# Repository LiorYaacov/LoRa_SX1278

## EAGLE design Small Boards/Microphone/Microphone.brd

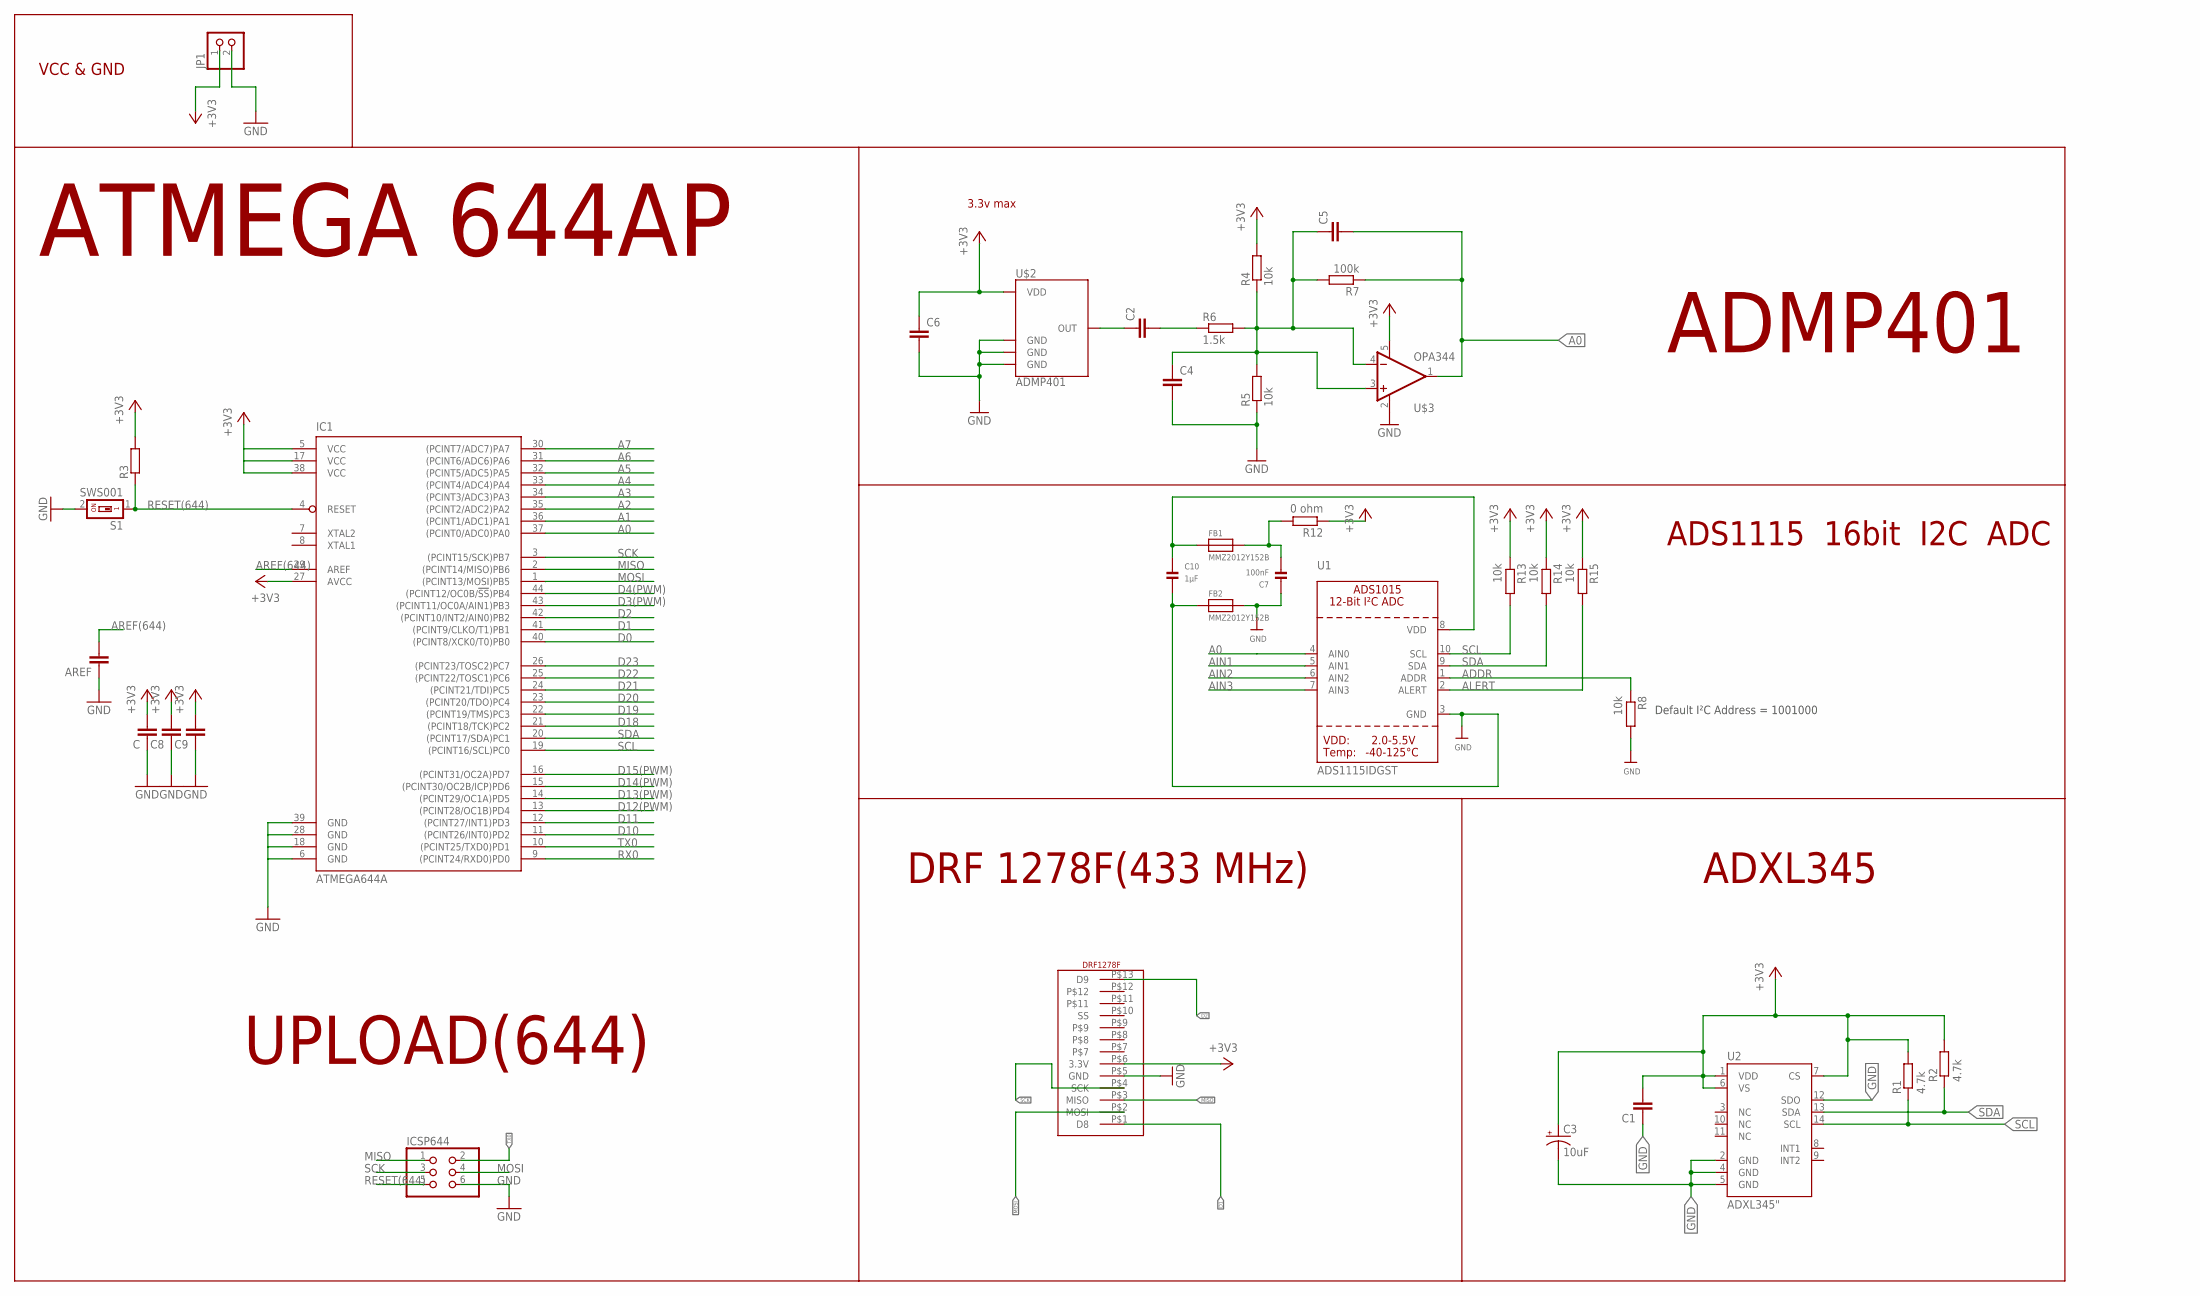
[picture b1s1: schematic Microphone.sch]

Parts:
AREF: 100nF; C0805
C: 22 uF; C0805
C1, C6: 0.1uF; C0805
C2: 4.7uF; C0805
C3: 10uF; EIA3216
C4: 1uF; C0805
C5: 100pF; C0805
C7: 100nF; 0805
C8, C9: 100nF; C0805
C10: 1µF; 0805
FB1, FB2: MMZ2012Y152B; 0805
IC1: ATMEGA644A; TQFP44
ICSP644: PINHD-2X3; 2X03
JP1: PINHD-1X2; 1X02
R1, R2: 4.7k; R0805
R3: R-EU_R0805; R0805
R4, R5, R8, R13, R14, R15: 10k; R0805
R6: 1.5k; R0805
R7: 100k; R0805
R12: 0 ohm; R0805
S1: SWS001; SMS-001
U1: ADS1115IDGST; MSOP10
U2: ADXL345"; ADXL3451:1
U$1: DRF1278F; DIP13
U$2: ADMP401
U$3: OPA344; SOT23-5

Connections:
+3V3: C.2, C1.2, C3.A (+), C6.1, C8.2, C9.2, IC1.5 (VCC), IC1.17 (VCC), IC1.27 (AVCC), IC1.38 (VCC), JP1.1, R1.2, R2.2, R3.2, R4.2, R12.1, R13.1, R14.1, R15.1, U2.1 (VDD), U2.6 (VS), U2.7 (CS), U$1.P$6 (3.3V), U$2.5 (VDD), U$3.5 (V+)
A0: C5.2, IC1.37 ((PCINT0/ADC0)PA0), R7.1, U1.4 (AIN0), U$3.1 (OUT)
A1: IC1.36 ((PCINT1/ADC1)PA1)
A2: IC1.35 ((PCINT2/ADC2)PA2)
A3: IC1.34 ((PCINT3/ADC3)PA3)
A4: IC1.33 ((PCINT4/ADC4)PA4)
A5: IC1.32 ((PCINT5/ADC5)PA5)
A6: IC1.31 ((PCINT6/ADC6)PA6)
A7: IC1.30 ((PCINT7/ADC7)PA7)
ADDR: R8.1, U1.1 (ADDR)
AIN1: U1.5 (AIN1)
AIN2: U1.6 (AIN2)
AIN3: U1.7 (AIN3)
ALERT: R15.2, U1.2 (ALERT)
AREF(644): AREF.2, IC1.29 (AREF)
D0: IC1.40 ((PCINT8/XCK0/T0)PB0)
D1: IC1.41 ((PCINT9/CLKO/T1)PB1), U$1.P$1 (D8)
D2: IC1.42 ((PCINT10/INT2/AIN0)PB2), U$1.P$13 (D9)
D3(PWM): IC1.43 ((PCINT11/OC0A/AIN1)PB3)
D4(PWM): IC1.44 ((PCINT12/OC0B/!SS!)PB4)
D10: IC1.11 ((PCINT26/INT0)PD2)
D11: IC1.12 ((PCINT27/INT1)PD3)
D12(PWM): IC1.13 ((PCINT28/OC1B)PD4)
D13(PWM): IC1.14 ((PCINT29/OC1A)PD5)
D14(PWM): IC1.15 ((PCINT30/OC2B/ICP)PD6)
D15(PWM): IC1.16 ((PCINT31/OC2A)PD7)
D18: IC1.21 ((PCINT18/TCK)PC2)
D19: IC1.22 ((PCINT19/TMS)PC3)
D20: IC1.23 ((PCINT20/TDO)PC4)
D21: IC1.24 ((PCINT21/TDI)PC5)
D22: IC1.25 ((PCINT22/TOSC1)PC6)
D23: IC1.26 ((PCINT23/TOSC2)PC7)
GND: AREF.1, C.1, C1.1, C3.C (-), C4.2, C6.2, C7.1, C8.1, C9.1, C10.2, FB2.1, FB2.2, IC1.6 (GND), IC1.18 (GND), IC1.28 (GND), IC1.39 (GND), ICSP644.6, JP1.2, R5.1, R8.2, S1.2, U1.3 (GND), U2.2 (GND), U2.4 (GND), U2.5 (GND), U2.12 (SDO), U$1.P$5 (GND), U$2.2 (GND), U$2.4 (GND), U$2.6 (GND), U$3.2 (V-)
MISO: IC1.2 ((PCINT14/MISO)PB6), ICSP644.1, U$1.P$3 (MISO)
MOSI: IC1.1 ((PCINT13/MOSI)PB5), ICSP644.4, U$1.P$2 (MOSI)
unnamed: C2.1, U$2.1 (OUT)
unnamed: C2.2, R6.1
unnamed: C4.1, C5.1, R4.1, R5.2, R6.2, R7.2, U$3.3 (+IN), U$3.4 (-IN)
unnamed: C7.2, FB1.2, R12.2
unnamed: C10.1, FB1.1, U1.8 (VDD)
RESET(644): IC1.4 (RESET), ICSP644.5, R3.1, S1.1
RX0: IC1.9 ((PCINT24/RXD0)PD0)
SCK: IC1.3 ((PCINT15/SCK)PB7), ICSP644.3, U$1.P$4 (SCK)
SCL: IC1.19 ((PCINT16/SCL)PC0), R1.1, R13.2, U1.10 (SCL), U2.14 (SCL)
SDA: IC1.20 ((PCINT17/SDA)PC1), R2.1, R14.2, U1.9 (SDA), U2.13 (SDA)
TX0: IC1.10 ((PCINT25/TXD0)PD1), ICSP644.2

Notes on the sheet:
ATMEGA 644AP
UPLOAD(644)
ADXL345
DRF 1278F(433 MHz)
VCC & GND
ADMP401
Default I²C Address = 1001000
ADS1115 16bit I2C ADC
3.3v max

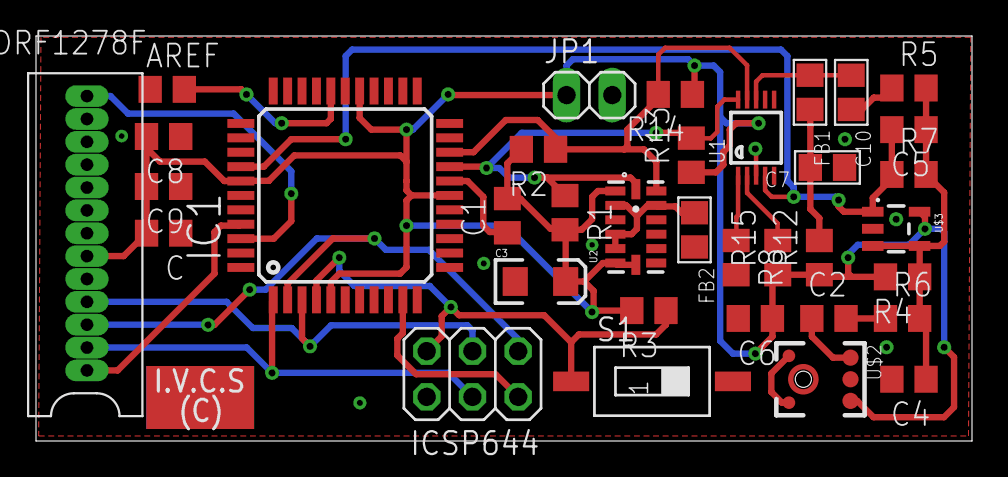
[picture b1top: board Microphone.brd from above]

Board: 2 copper layers, 52.0 x 22.5 mm, 35 parts (0 on the bottom side), 20 nets.

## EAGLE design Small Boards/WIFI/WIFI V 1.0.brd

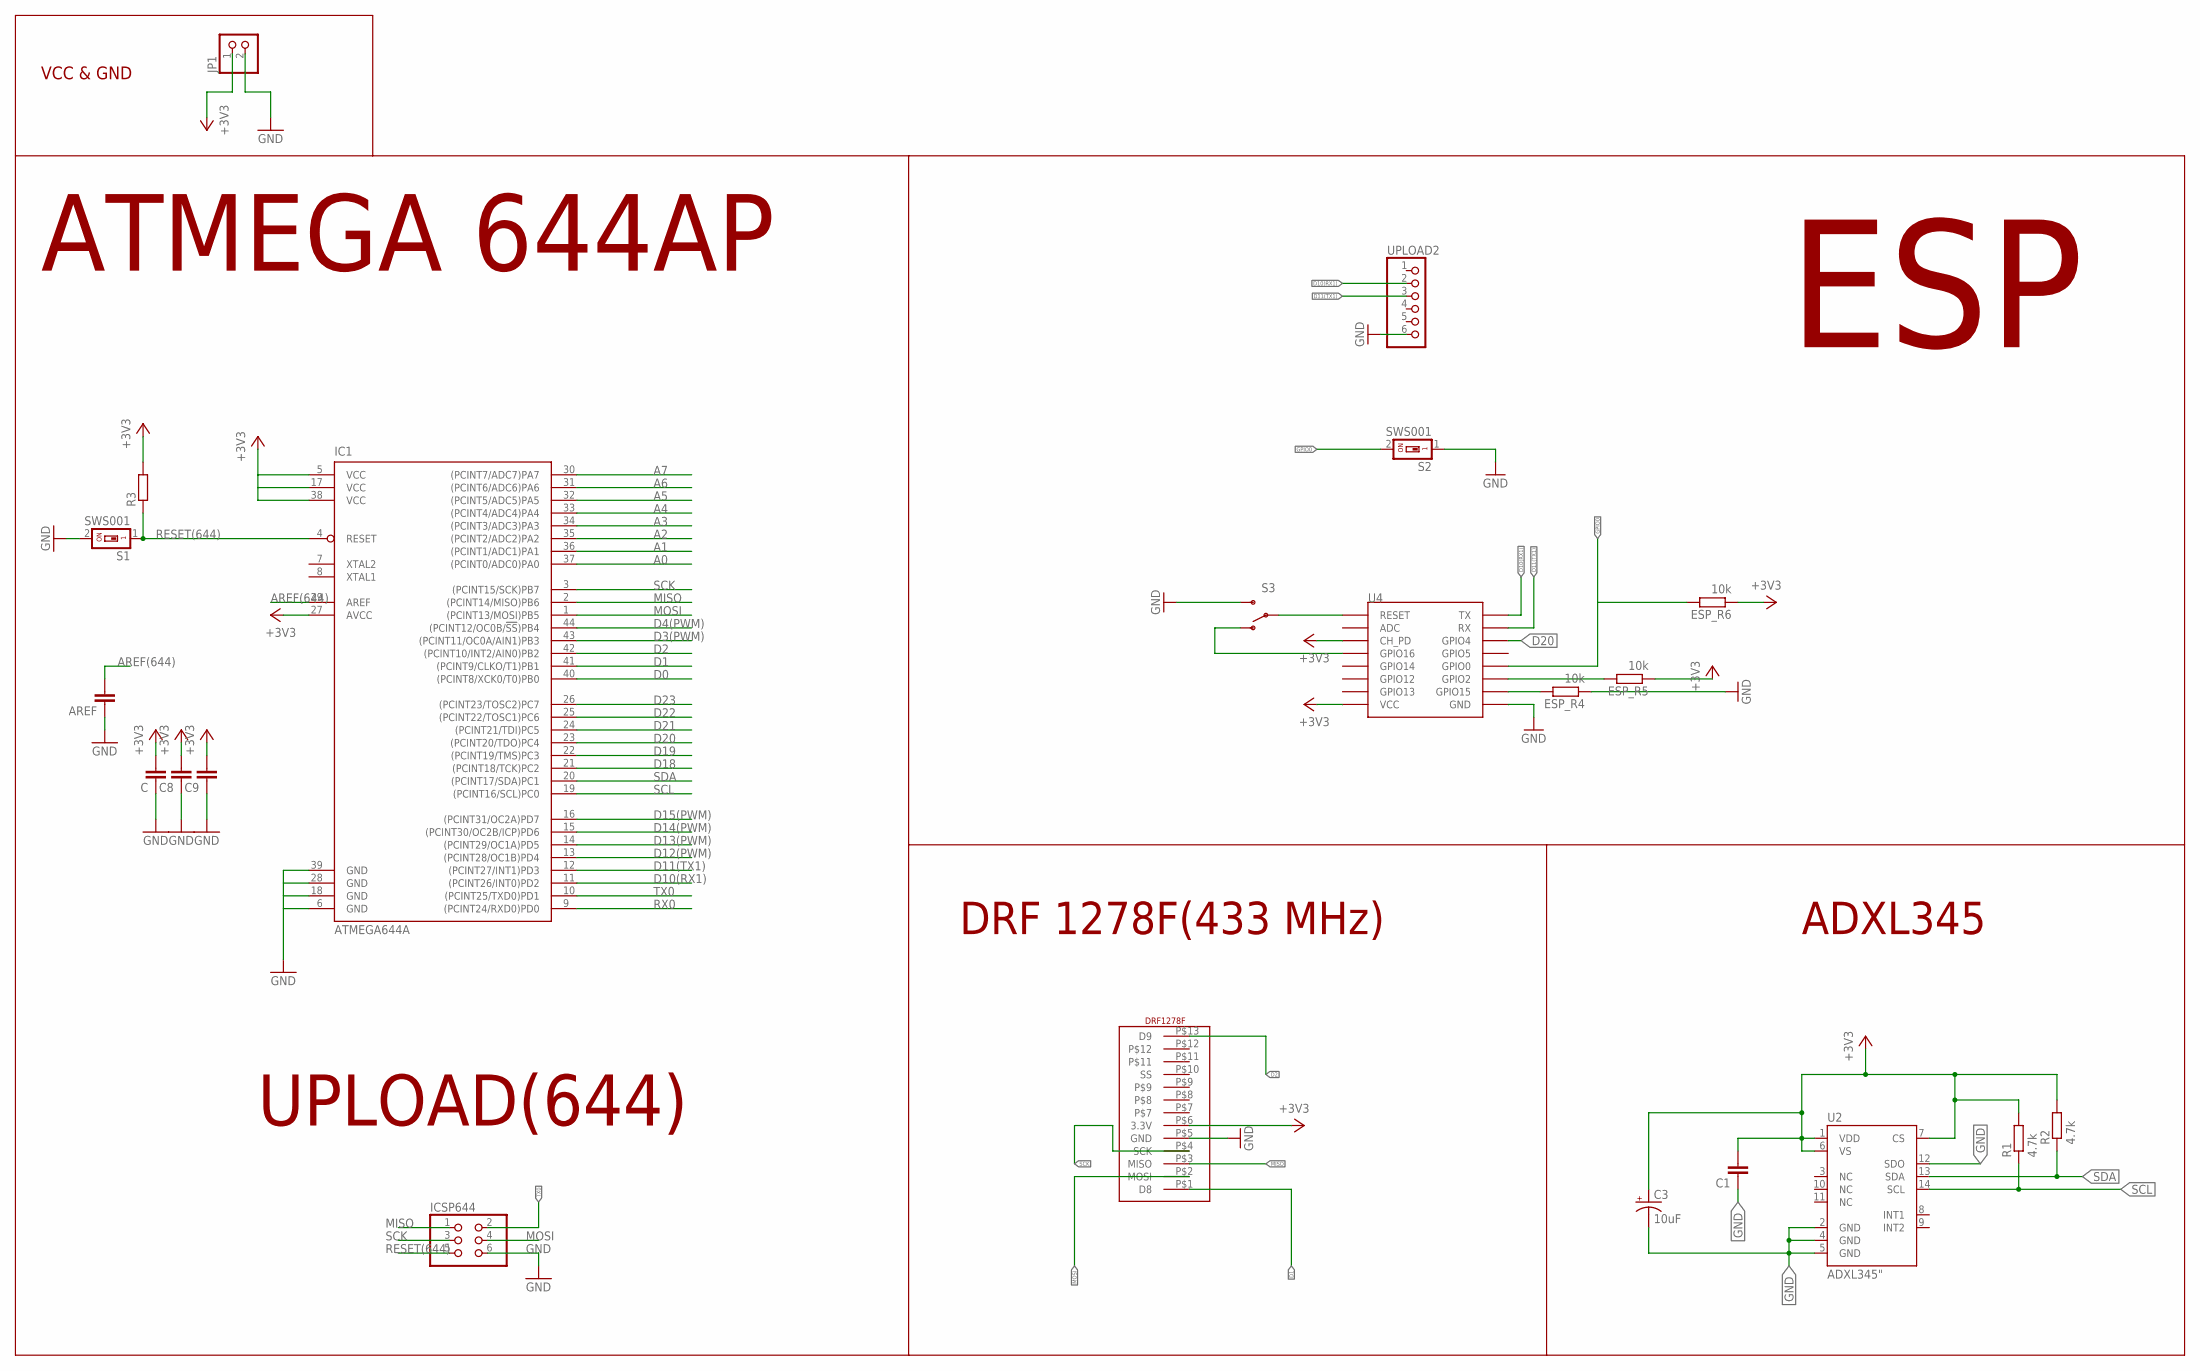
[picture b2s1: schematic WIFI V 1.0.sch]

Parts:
AREF: 100nF; C0805
C: 22 uF; C0805
C1: 0.1uF; C0805
C3: 10uF; EIA3216
C8, C9: 100nF; C0805
ESP_R4, ESP_R5, ESP_R6: 10k; R0805
IC1: ATMEGA644A; TQFP44
ICSP644: PINHD-2X3; 2X03
JP1: PINHD-1X2; 1X02
R1, R2: 4.7k; R0805
R3: R-EU_R0805; R0805
S1, S2: SWS001; SMS-001
S3: SWITCH-SPDTPTH; SWITCH-SPDT
U2: ADXL345"; ADXL3451:1
U4: ESP12SMD; ESP12-SMD
U$1: DRF1278F; DIP13
UPLOAD2: PINHD-1X6; 1X06

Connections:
+3V3: C.2, C1.2, C3.A (+), C8.2, C9.2, ESP_R5.1, ESP_R6.1, IC1.5 (VCC), IC1.17 (VCC), IC1.27 (AVCC), IC1.38 (VCC), JP1.1, R1.2, R2.2, R3.2, U2.1 (VDD), U2.6 (VS), U2.7 (CS), U4.CH_PD, U4.VCC, U$1.P$6 (3.3V)
A0: IC1.37 ((PCINT0/ADC0)PA0)
A1: IC1.36 ((PCINT1/ADC1)PA1)
A2: IC1.35 ((PCINT2/ADC2)PA2)
A3: IC1.34 ((PCINT3/ADC3)PA3)
A4: IC1.33 ((PCINT4/ADC4)PA4)
A5: IC1.32 ((PCINT5/ADC5)PA5)
A6: IC1.31 ((PCINT6/ADC6)PA6)
A7: IC1.30 ((PCINT7/ADC7)PA7)
AREF(644): AREF.2, IC1.29 (AREF)
D0: IC1.40 ((PCINT8/XCK0/T0)PB0)
D1: IC1.41 ((PCINT9/CLKO/T1)PB1), U$1.P$1 (D8)
D2: IC1.42 ((PCINT10/INT2/AIN0)PB2), U$1.P$13 (D9)
D3(PWM): IC1.43 ((PCINT11/OC0A/AIN1)PB3)
D4(PWM): IC1.44 ((PCINT12/OC0B/!SS!)PB4)
D10(RX1): IC1.11 ((PCINT26/INT0)PD2), U4.TXD0 (TX), UPLOAD2.2
D11(TX1): IC1.12 ((PCINT27/INT1)PD3), U4.RXD0 (RX), UPLOAD2.3
D12(PWM): IC1.13 ((PCINT28/OC1B)PD4)
D13(PWM): IC1.14 ((PCINT29/OC1A)PD5)
D14(PWM): IC1.15 ((PCINT30/OC2B/ICP)PD6)
D15(PWM): IC1.16 ((PCINT31/OC2A)PD7)
D18: IC1.21 ((PCINT18/TCK)PC2)
D19: IC1.22 ((PCINT19/TMS)PC3)
D20: IC1.23 ((PCINT20/TDO)PC4), U4.GPIO4
D21: IC1.24 ((PCINT21/TDI)PC5)
D22: IC1.25 ((PCINT22/TOSC1)PC6)
D23: IC1.26 ((PCINT23/TOSC2)PC7)
GND: AREF.1, C.1, C1.1, C3.C (-), C8.1, C9.1, ESP_R4.1, IC1.6 (GND), IC1.18 (GND), IC1.28 (GND), IC1.39 (GND), ICSP644.6, JP1.2, S1.2, S2.1, S3.3 (S), U2.2 (GND), U2.4 (GND), U2.5 (GND), U2.12 (SDO), U4.GND, U$1.P$5 (GND), UPLOAD2.6
GPIO0: ESP_R6.2, S2.2, U4.GPIO0
MISO: IC1.2 ((PCINT14/MISO)PB6), ICSP644.1, U$1.P$3 (MISO)
MOSI: IC1.1 ((PCINT13/MOSI)PB5), ICSP644.4, U$1.P$2 (MOSI)
unnamed: S3.1 (O), U4.GPIO16
unnamed: S3.2, U4.RESET
unnamed: ESP_R4.2, U4.GPIO15
unnamed: ESP_R5.2, U4.GPIO2
RESET(644): IC1.4 (RESET), ICSP644.5, R3.1, S1.1
RX0: IC1.9 ((PCINT24/RXD0)PD0)
SCK: IC1.3 ((PCINT15/SCK)PB7), ICSP644.3, U$1.P$4 (SCK)
SCL: IC1.19 ((PCINT16/SCL)PC0), R1.1, U2.14 (SCL)
SDA: IC1.20 ((PCINT17/SDA)PC1), R2.1, U2.13 (SDA)
TX0: IC1.10 ((PCINT25/TXD0)PD1), ICSP644.2

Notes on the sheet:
ATMEGA 644AP
UPLOAD(644)
ADXL345
DRF 1278F(433 MHz)
VCC & GND
ESP

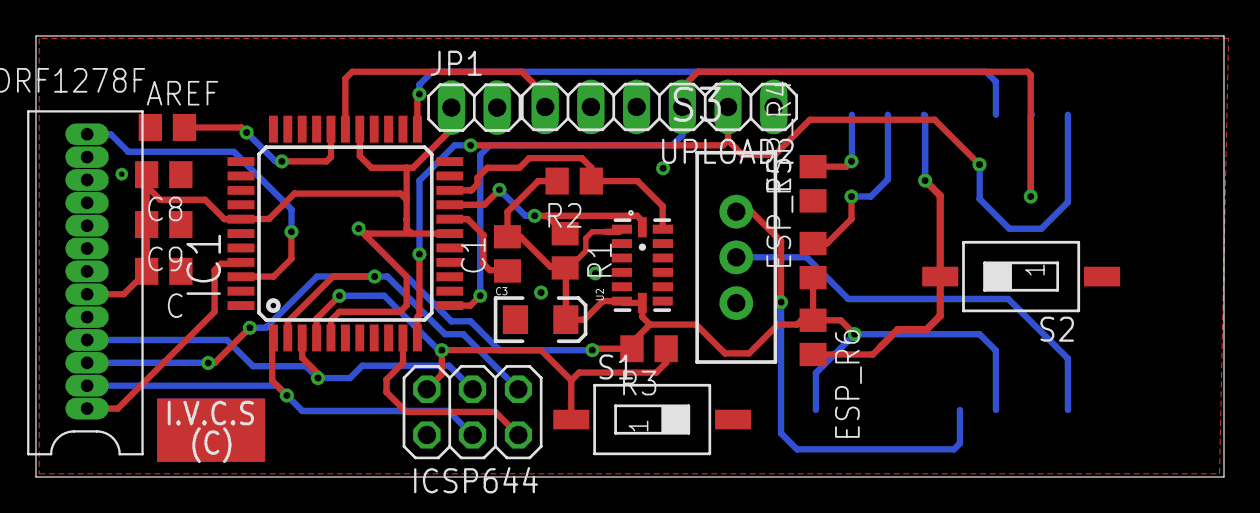
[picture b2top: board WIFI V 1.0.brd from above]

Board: 2 copper layers, 66.0 x 24.5 mm, 22 parts (1 on the bottom side), 20 nets.

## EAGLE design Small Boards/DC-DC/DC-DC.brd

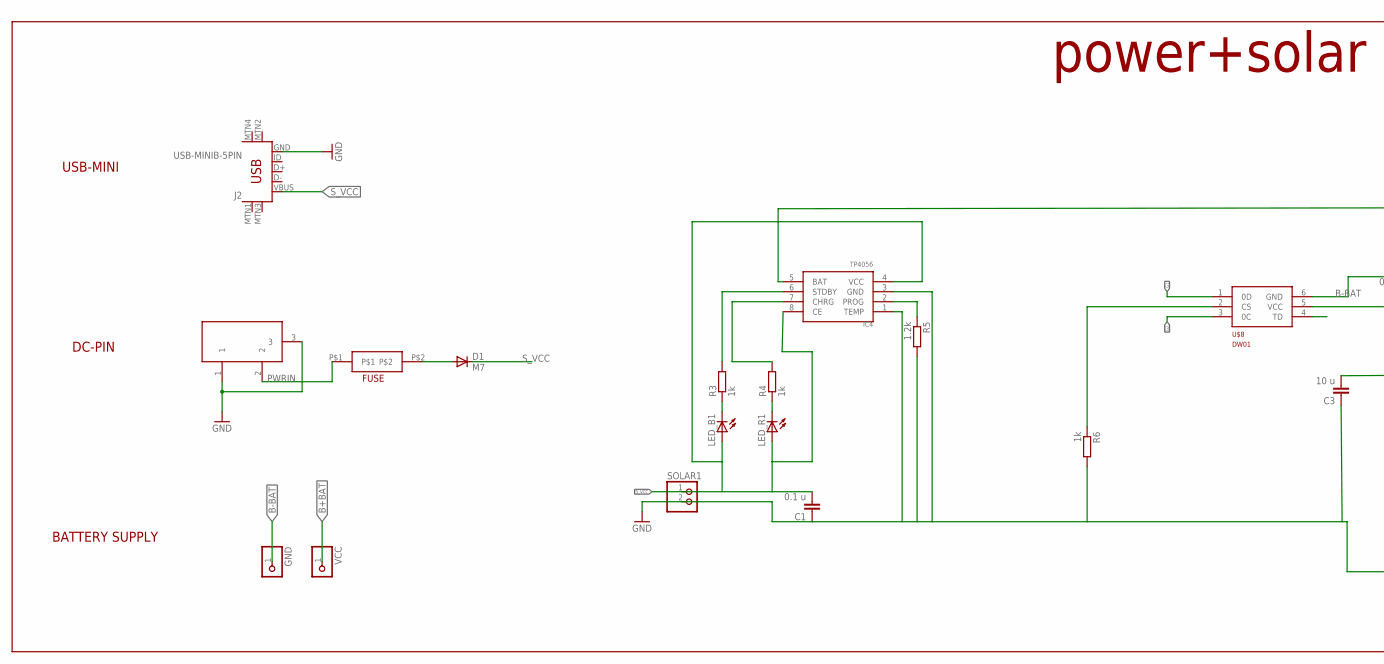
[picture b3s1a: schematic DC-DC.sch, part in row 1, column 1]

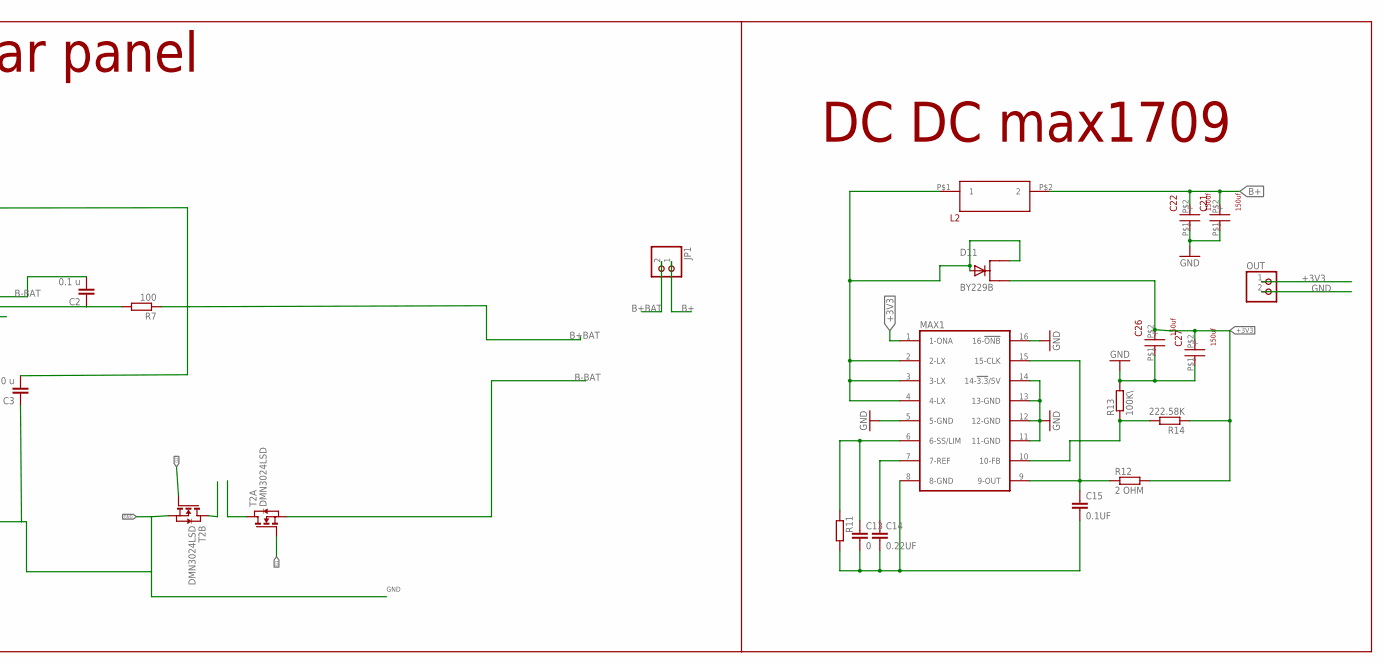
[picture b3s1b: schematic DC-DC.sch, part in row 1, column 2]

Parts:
C1, C2: 0.1 u; C0805
C3: 10 u; C0805
C13: 0; C0805
C14: 0.22UF; C0805
C15: 0.1UF; C0805
C21, C22, C26, C27: 150uf; CAP
D1: M7; SMB
D11: BY229B; TO263AB
GND: PINHD-1X1; 1X01
IC4: TP4056; SOP-8
J2: USB-MINIB-5PIN; USB-MINIB
JP1: PINHD-1X2; 1X02
L2: INDUCTOR; INDUCTOR_150
LED_B1: LEDCHIP-LED0805; CHIP-LED0805
LED_R1: LEDCHIP-LED0805; CHIP-LED0805
MAX1: MOSHE_MAX1709F; MAX1709
OUT: PINHD-1X2; 1X02
R3, R4, R6: 1k; R0805
R5: 1.2k; R0805
R7: 100; R0805
R11: R-EU_R0805; R0805
R12: 2 OHM; R0805
R13: 100K\; R0805
R14: 222.58K; R0805
SOLAR1: PINHD-1X2; 1X02
T2: DMN3024LSD; TSSOP-8
U$5: FUSE_M; DIP2
U$8: DW01; SOT23-6
VCC: PINHD-1X1; 1X01
X1: DC21MMX; DC-21MM

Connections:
+3V3: C26.P$2 (-), C27.P$2 (-), D11.K, MAX1.1 (1-ONA), OUT.1, R12.2, R14.1
B+: C21.P$2 (-), C22.P$2 (-), JP1.1, L2.P$2 (2)
B+BAT: C3.2, IC4.5 (BAT), JP1.2, R7.1, VCC.1
B-BAT: C2.2, GND.1, T2.2 (S), T2.3 (S), U$8.6 (GND)
G1: T2.4 (G), U$8.1 (0D)
G2: T2.5 (G), U$8.3 (0C)
GND: C1.1, C3.1, C13.2, C14.2, C15.2, C21.P$1 (+), C22.P$1 (+), C26.P$1 (+), C27.P$1 (+), IC4.1 (TEMP), IC4.3 (GND), J2.GND, MAX1.5 (5-GND), MAX1.8 (8-GND), MAX1.11 (11-GND), MAX1.12 (12-GND), MAX1.13 (13-GND), MAX1.14 (14-!3.3!/5V), MAX1.16 (16-!ONB!), OUT.2, R5.2, R6.2, R11.2, R13.2, SOLAR1.2, T2.6 (S), T2.7 (S), X1.1, X1.3
unnamed: LED_B1.C, R3.1
unnamed: LED_R1.C, R4.1
unnamed: D1.A, U$5.P$2
unnamed: IC4.6 (STDBY), R3.2
unnamed: C13.1, MAX1.6 (6-SS/LIM), R11.1
unnamed: C14.1, MAX1.7 (7-REF)
unnamed: IC4.7 (CHRG), R4.2
unnamed: IC4.2 (PROG), R5.1
unnamed: R6.1, U$8.2 (CS)
unnamed: C2.1, R7.2, U$8.5 (VCC)
unnamed: C15.1, MAX1.9 (9-OUT), MAX1.15 (15-CLK), R12.1
unnamed: MAX1.10 (10-FB), R13.1, R14.2
unnamed: D11.1, D11.2, L2.P$1 (1), MAX1.2 (2-LX), MAX1.3 (3-LX), MAX1.4 (4-LX)
PWRIN: U$5.P$1, X1.2
S_VCC: C1.2, D1.C, IC4.4 (VCC), IC4.8 (CE), J2.VBUS, LED_B1.A, LED_R1.A, SOLAR1.1

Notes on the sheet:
DC DC max1709
power+solar panel
USB-MINI
DC-PIN
BATTERY SUPPLY

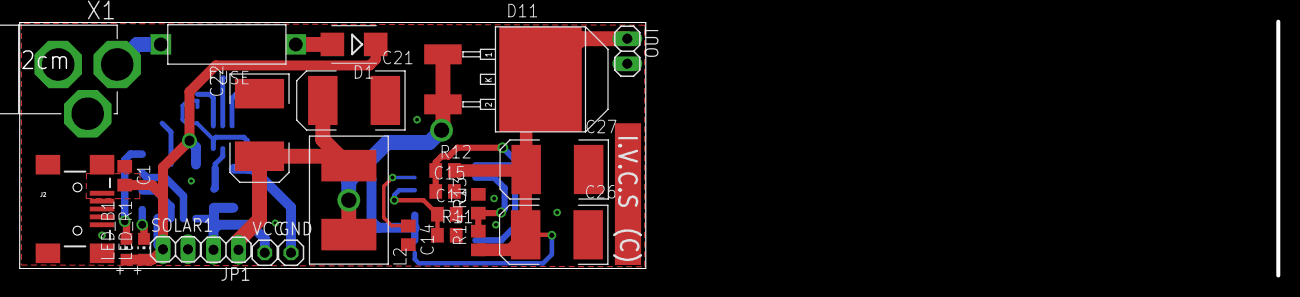
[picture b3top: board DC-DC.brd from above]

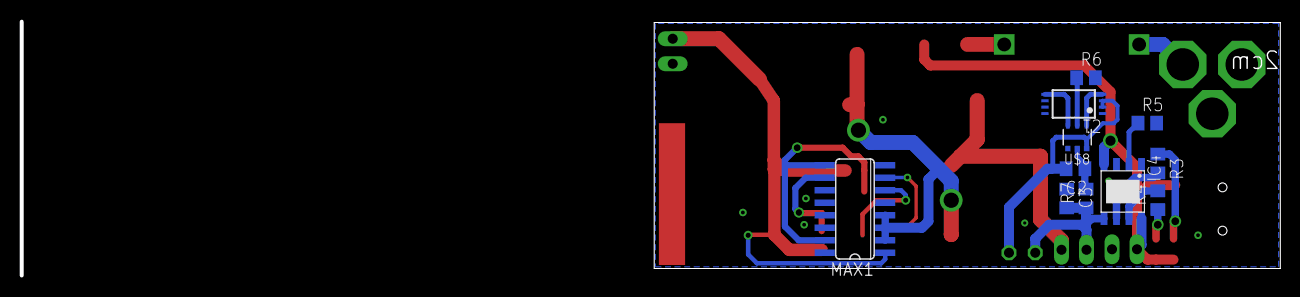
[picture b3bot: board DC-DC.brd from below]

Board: 2 copper layers, 127.6 x 25.8 mm, 36 parts (11 on the bottom side), 22 nets.

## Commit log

2021-11-08 Small Boards

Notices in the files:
parts and their libraries:
SparkFun-Connectors: Licensing: Creative Commons ShareAlike 4.0 International - https://creativecommons.org/licenses/by-sa/4.0
